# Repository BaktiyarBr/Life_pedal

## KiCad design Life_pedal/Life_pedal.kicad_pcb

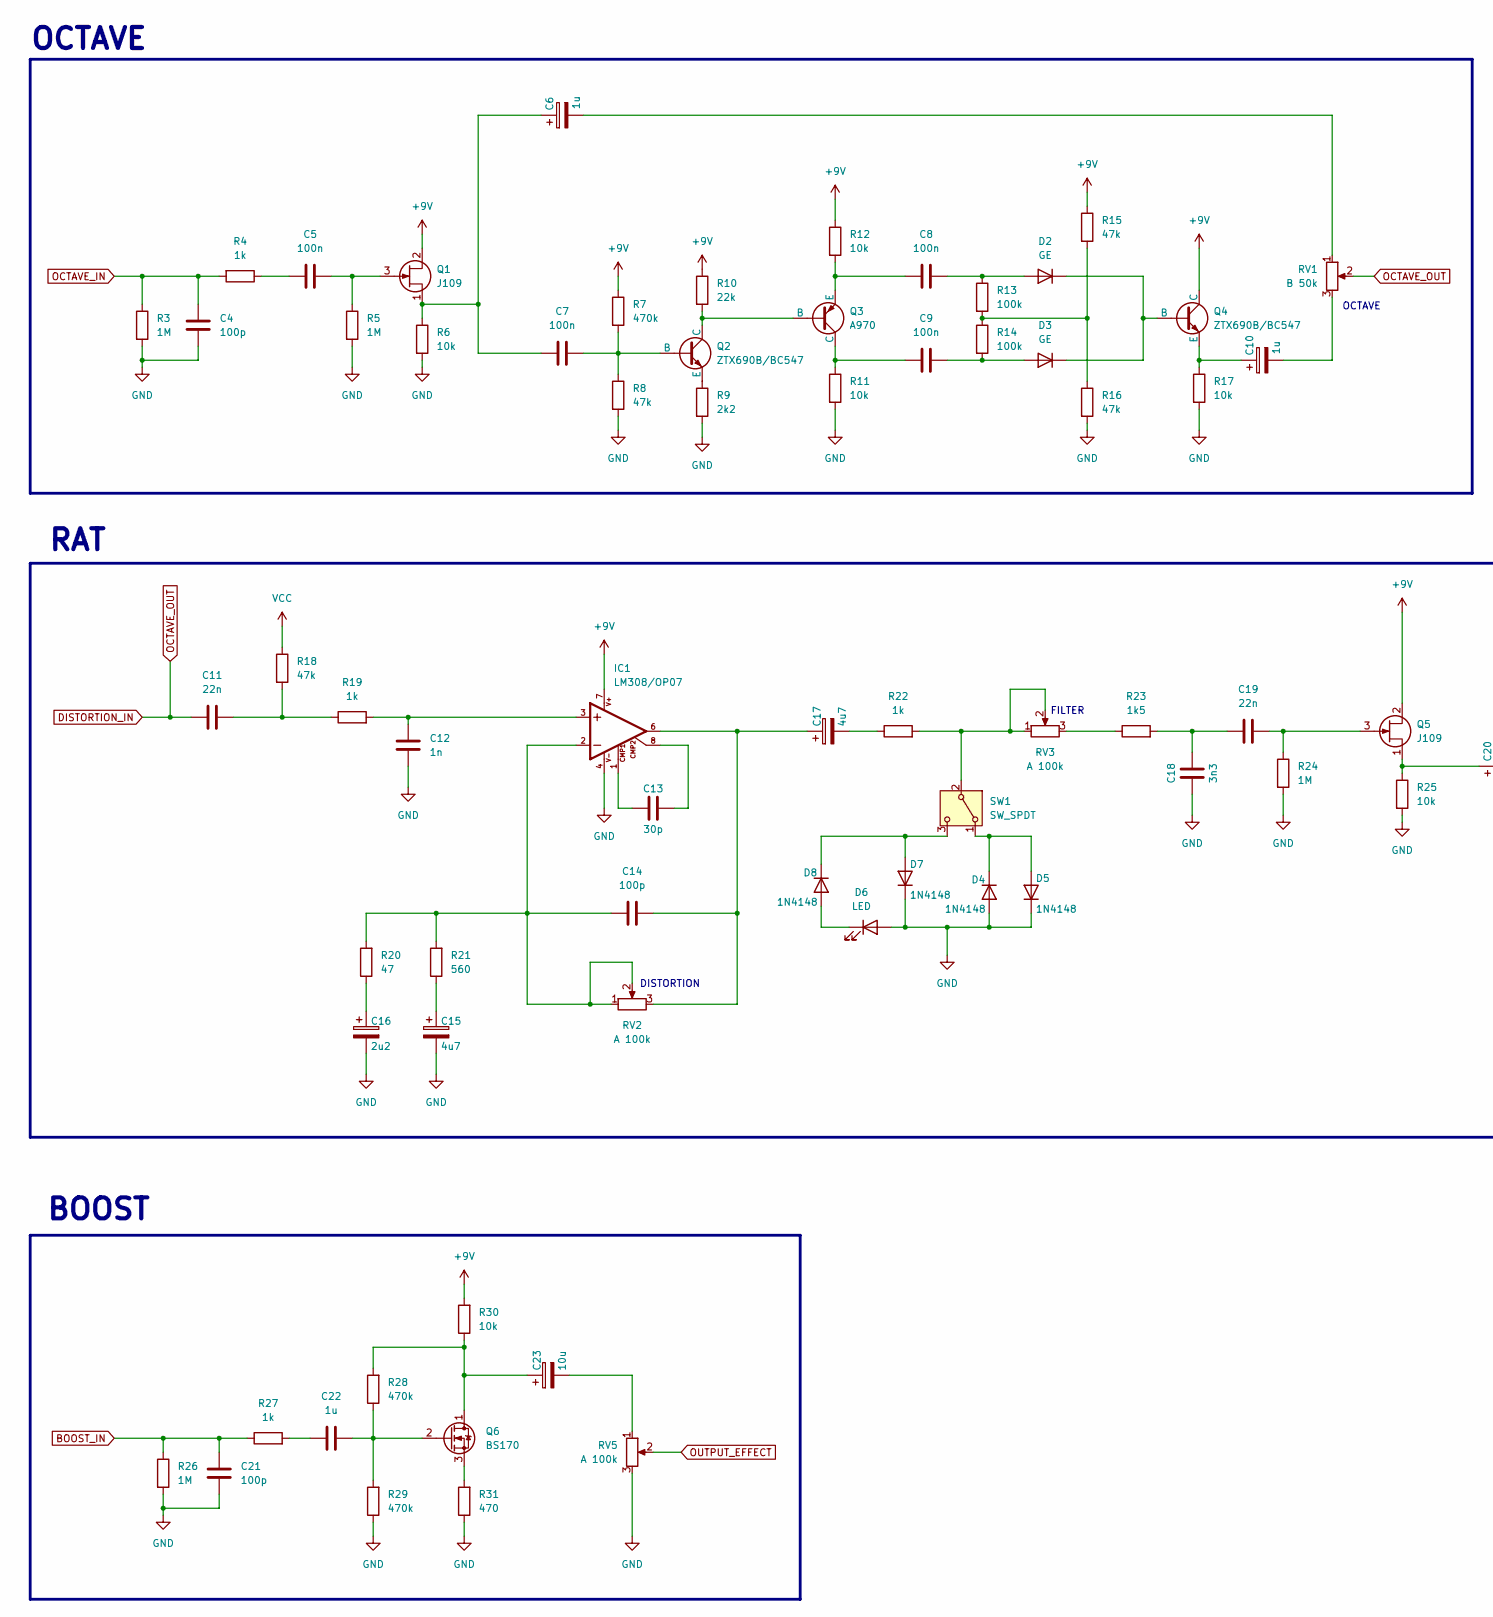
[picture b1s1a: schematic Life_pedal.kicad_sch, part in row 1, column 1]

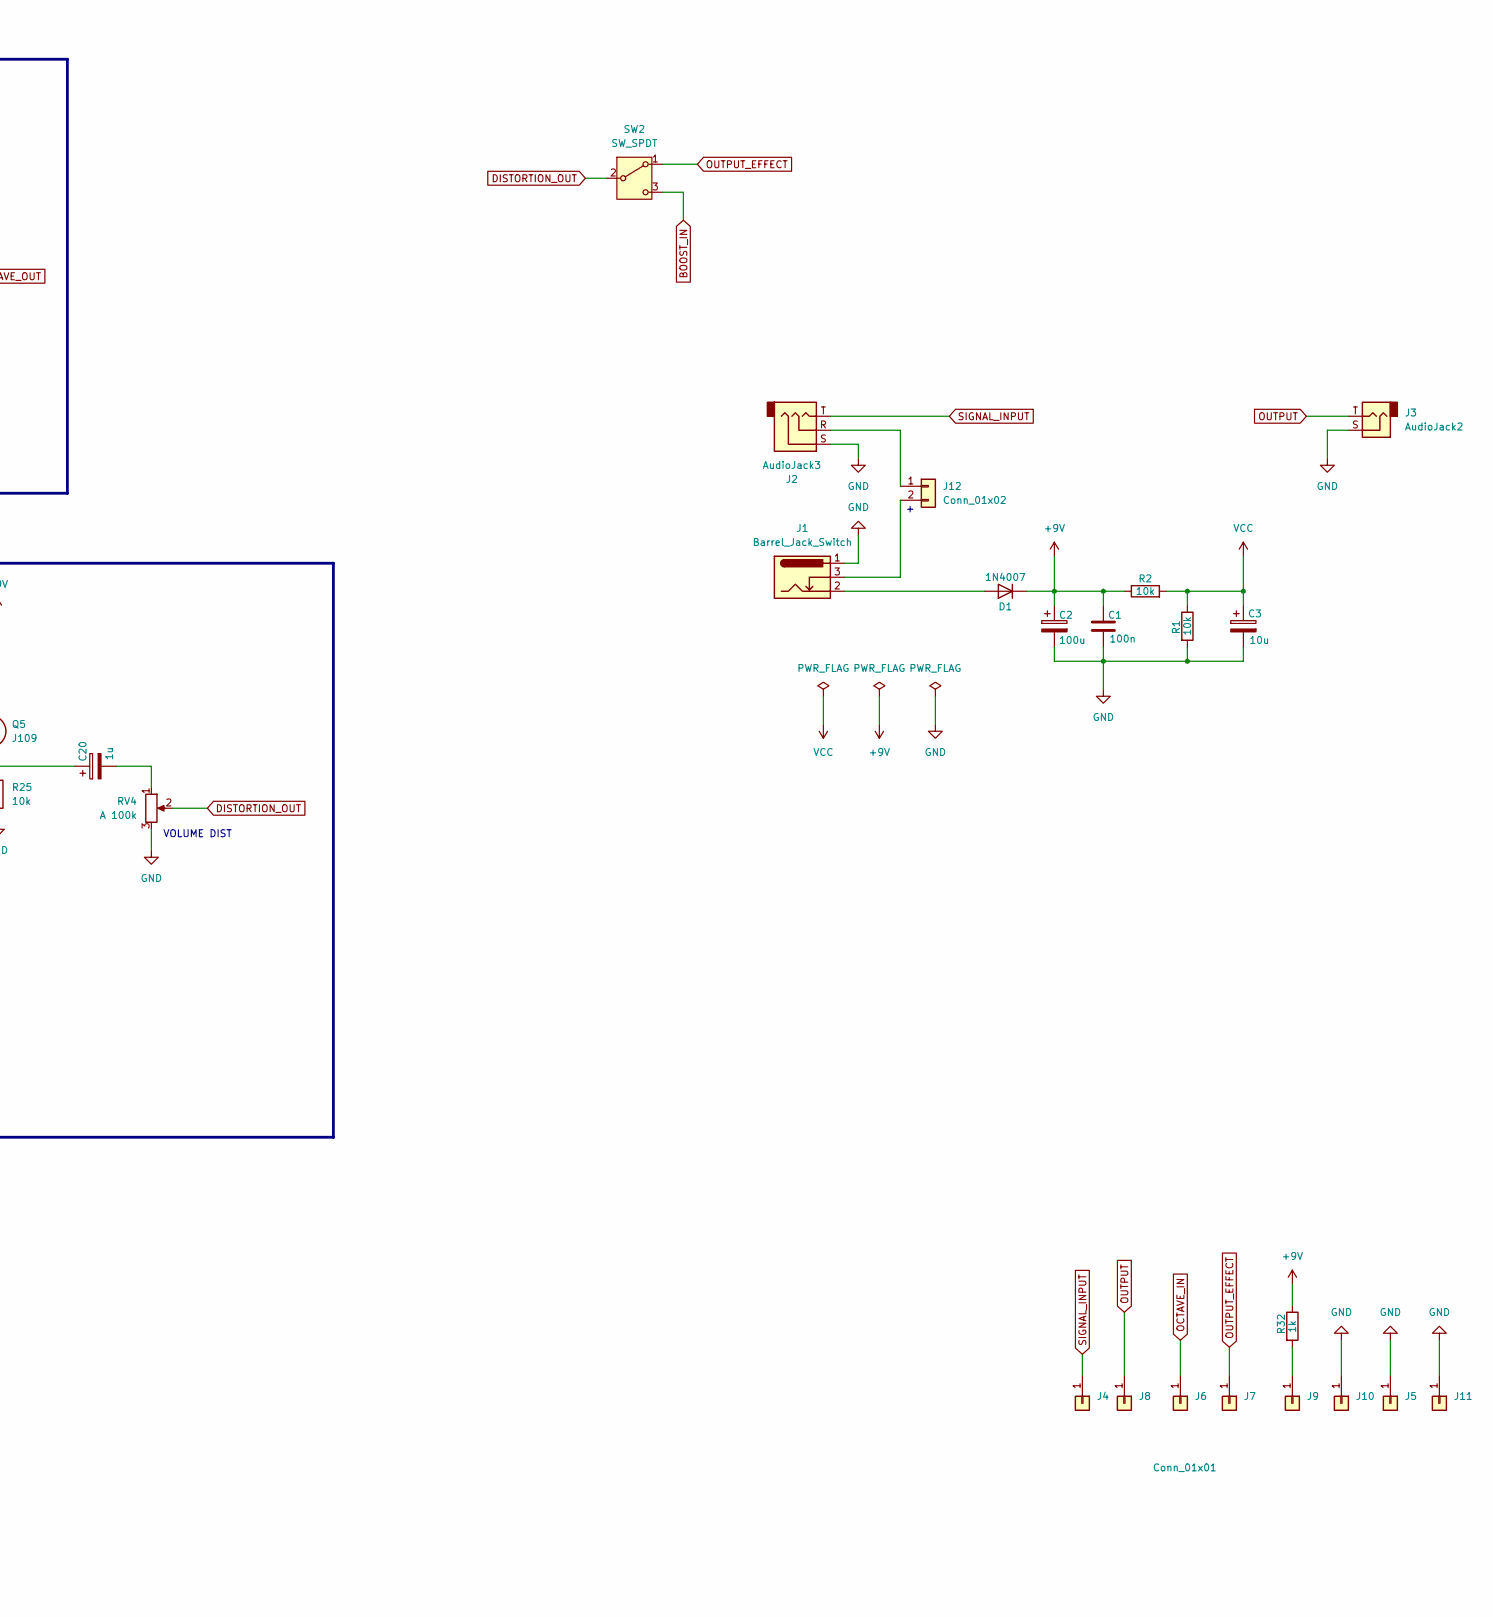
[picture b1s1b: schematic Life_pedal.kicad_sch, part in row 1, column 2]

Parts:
C1, C5, C7, C8, C9: 100n; C_0603_1608Metric_Pad1.08x0.95mm_HandSolder
C2: 100u; CP_Radial_D5.0mm_P2.50mm
C3, C23: 10u; CP_Radial_D5.0mm_P2.50mm
C4, C14, C21: 100p; C_0603_1608Metric_Pad1.08x0.95mm_HandSolder
C6, C10, C20: 1u; CP_Radial_D5.0mm_P2.50mm
C11, C19: 22n; C_0603_1608Metric_Pad1.08x0.95mm_HandSolder
C12: 1n; C_0603_1608Metric_Pad1.08x0.95mm_HandSolder
C13: 30p; C_0603_1608Metric_Pad1.08x0.95mm_HandSolder
C15, C17: 4u7; CP_Radial_D5.0mm_P2.50mm
C16: 2u2; CP_Radial_D5.0mm_P2.50mm
C18: 3n3; C_0603_1608Metric_Pad1.08x0.95mm_HandSolder
C22: 1u; C_0603_1608Metric_Pad1.08x0.95mm_HandSolder
D1: 1N4007; D_DO-41_SOD81_P2.54mm_Vertical_KathodeUp
D2, D3: GE; D_DO-41_SOD81_P2.54mm_Vertical_KathodeUp
D4, D5, D7, D8: 1N4148; D_DO-41_SOD81_P2.54mm_Vertical_KathodeUp
D6: LED; D_DO-41_SOD81_P2.54mm_Vertical_KathodeUp
IC1: LM308/OP07; DIL08
J1: Barrel_Jack_Switch; BarrelJack_GCT_DCJ200-10-A_Horizontal
J2: AudioJack3; Jack_6.35mm_Neutrik_NMJ6HCD2_Horizontal
J3: AudioJack2; Jack_6.35mm_Neutrik_NMJ6HCD2_Horizontal
J4, J5, J6, J7, J8, J9, J10, J11: Conn_01x01; SolderWire-2sqmm_1x01_D2mm_OD3.9mm
J12: Conn_01x02; PinSocket_1x02_P2.54mm_Vertical
Q1, Q5: J109; TO-92L_Inline_Wide
Q2, Q4: ZTX690B/BC547; TO-92L_Inline_Wide
Q3: A970; TO-92L_Inline_Wide
Q6: BS170; TO-92_Inline
R1, R2, R6, R11, R12, R17, R25, R30: 10k; R_0603_1608Metric_Pad0.98x0.95mm_HandSolder
R3, R5, R24, R26: 1M; R_0603_1608Metric_Pad0.98x0.95mm_HandSolder
R4, R19, R22, R27, R32: 1k; R_0603_1608Metric_Pad0.98x0.95mm_HandSolder
R7, R28, R29: 470k; R_0603_1608Metric_Pad0.98x0.95mm_HandSolder
R8, R15, R16, R18: 47k; R_0603_1608Metric_Pad0.98x0.95mm_HandSolder
R9: 2k2; R_0603_1608Metric_Pad0.98x0.95mm_HandSolder
R10: 22k; R_0603_1608Metric_Pad0.98x0.95mm_HandSolder
R13, R14: 100k; R_0603_1608Metric_Pad0.98x0.95mm_HandSolder
R20: 47; R_0603_1608Metric_Pad0.98x0.95mm_HandSolder
R21: 560; R_0603_1608Metric_Pad0.98x0.95mm_HandSolder
R23: 1k5; R_0603_1608Metric_Pad0.98x0.95mm_HandSolder
R31: 470; R_0603_1608Metric_Pad0.98x0.95mm_HandSolder
RV1: B 50k; Potentiometer_Omeg_PC16BU_Vertical
RV2, RV3, RV4, RV5: A 100k; Potentiometer_Omeg_PC16BU_Vertical
SW1, SW2: SW_SPDT; SW_Slide-03_Wuerth-WS-SLTV_10x2.5x6.4_P2.54mm

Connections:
+9V: C1.1, C2.1, D1.1 (K), IC1.7, Q1.2 (S), Q4.1 (C), Q5.2 (S), R2.1, R7.1, R10.1, R12.1, R15.1, R30.2, R32.1
BOOST_IN: C21.1, R26.1, R27.1, SW2.3 (C)
DISTORTION_IN: C11.2, RV1.2
DISTORTION_OUT: RV4.2, SW2.2 (B)
GND: C1.2, C2.2, C3.2, C4.1, C12.2, C15.2, C16.2, C18.1, C21.2, D4.2 (A), D5.1 (K), D6.2 (A), D7.1 (K), IC1.4, J1.1, J2.S, J3.S, J5.1, J10.1, J11.1, R1.2, R3.2, R5.2, R6.2, R8.2, R9.2, R11.2, R16.2, R17.2, R24.2, R25.2, R26.2, R29.1, R31.1, RV4.3, RV5.3
unnamed: C5.2, R4.1
unnamed: C6.2, RV1.1
unnamed: C10.2, RV1.3
unnamed: C11.1, R18.2, R19.1
unnamed: C12.1, IC1.3, R19.2
unnamed: C13.1, IC1.1
unnamed: C13.2, IC1.8
unnamed: C14.1, C17.1, IC1.6, RV2.3
unnamed: C14.2, IC1.2, R20.2, R21.2, RV2.1, RV2.2
unnamed: C15.1, R21.1
unnamed: C16.1, R20.1
unnamed: C17.2, R22.1
unnamed: C18.2, C19.2, R23.2
unnamed: C20.2, RV4.1
unnamed: C22.1, R27.2
unnamed: C23.2, RV5.1
unnamed: D1.2 (A), J1.2
unnamed: C8.1, D2.2 (A), R13.1
unnamed: D2.1 (K), D3.1 (K), Q4.2 (B)
unnamed: C9.1, D3.2 (A), R14.2
unnamed: D4.1 (K), D5.2 (A), SW1.1 (A)
unnamed: D6.1 (K), D8.2 (A)
unnamed: D7.2 (A), D8.1 (K), SW1.3 (C)
unnamed: J9.1, R32.2
unnamed: J2.R, J12.1
unnamed: J1.3, J12.2
unnamed: C6.1, C7.2, Q1.1 (D), R6.1
unnamed: C5.1, Q1.3 (G), R5.1
unnamed: C7.1, Q2.2 (B), R7.2, R8.1
unnamed: Q2.1 (C), Q3.3 (B), R10.2
unnamed: Q2.3 (E), R9.1
unnamed: C9.2, Q3.2 (C), R11.1
unnamed: C8.2, Q3.1 (E), R12.2
unnamed: C10.1, Q4.3 (E), R17.1
unnamed: C20.1, Q5.1 (D), R25.1
unnamed: C19.1, Q5.3 (G), R24.1
unnamed: C23.1, Q6.1 (D), R28.2, R30.1
unnamed: C22.2, Q6.2 (G), R28.1, R29.2
unnamed: Q6.3 (S), R31.2
unnamed: R13.2, R14.1, R15.2, R16.1
unnamed: R23.1, RV3.3
unnamed: R22.2, RV3.1, RV3.2, SW1.2 (B)
OCTAVE_IN: C4.2, J6.1, R3.1, R4.2
OUTPUT: J3.T, J8.1
OUTPUT_EFFECT: J7.1, RV5.2, SW2.1 (A)
SIGNAL_INPUT: J2.T, J4.1
VCC: C3.1, R1.1, R2.2, R18.1

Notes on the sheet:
OCTAVE
BOOST
RAT
VOLUME DIST
DISTORTION
FILTER

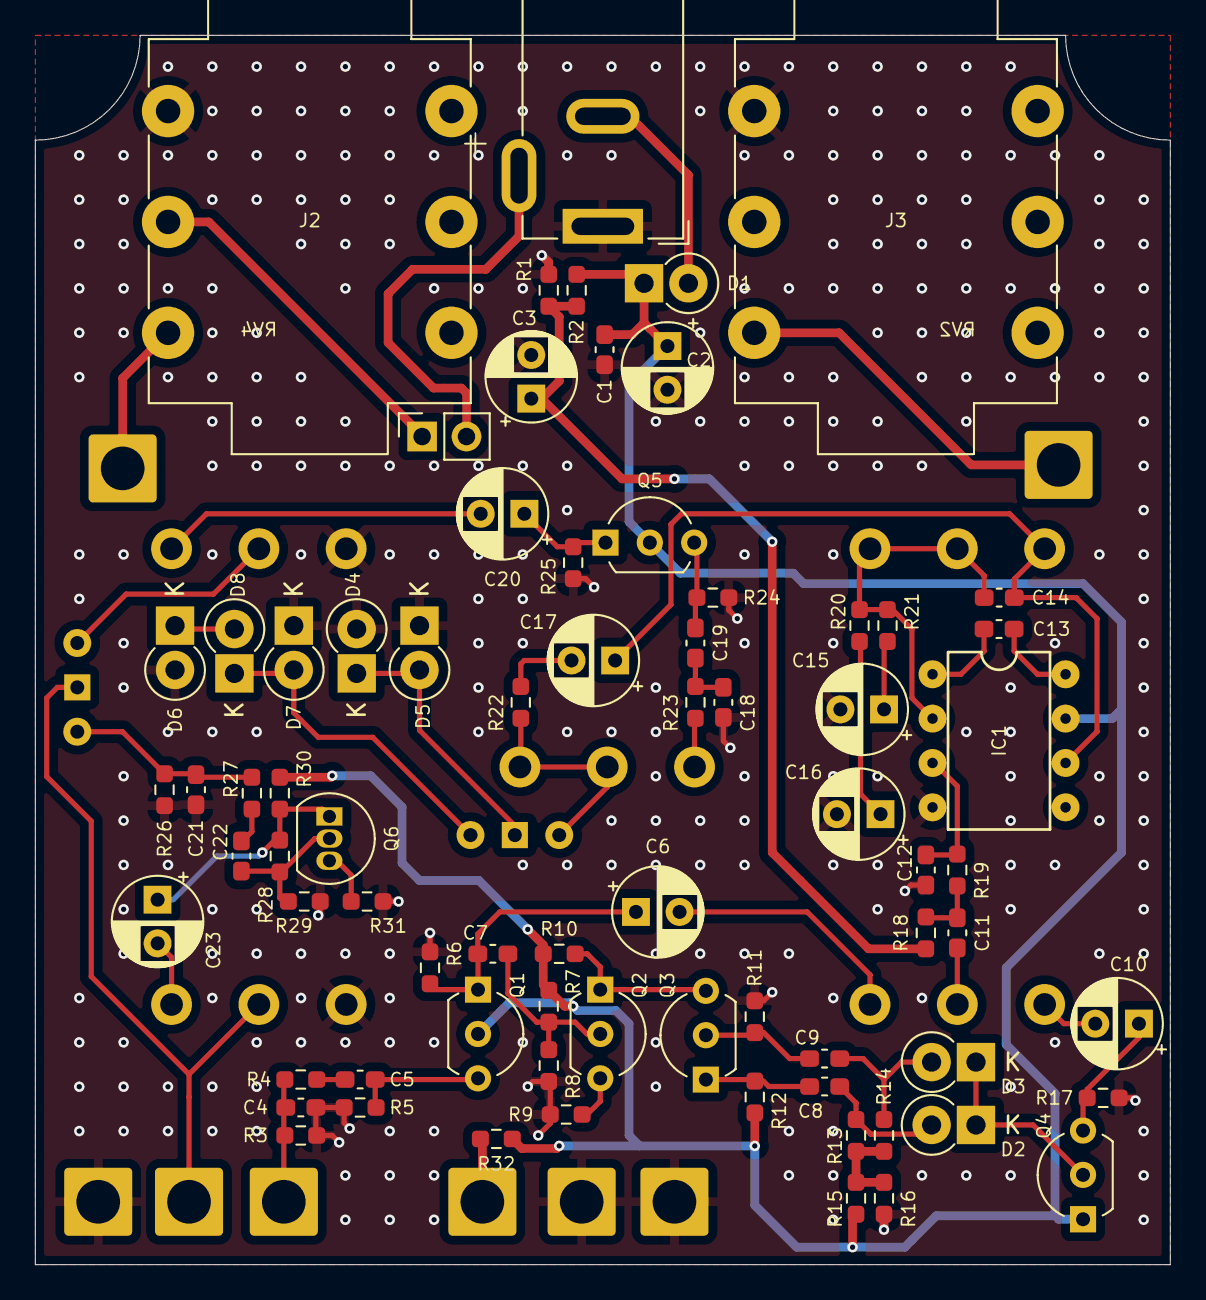
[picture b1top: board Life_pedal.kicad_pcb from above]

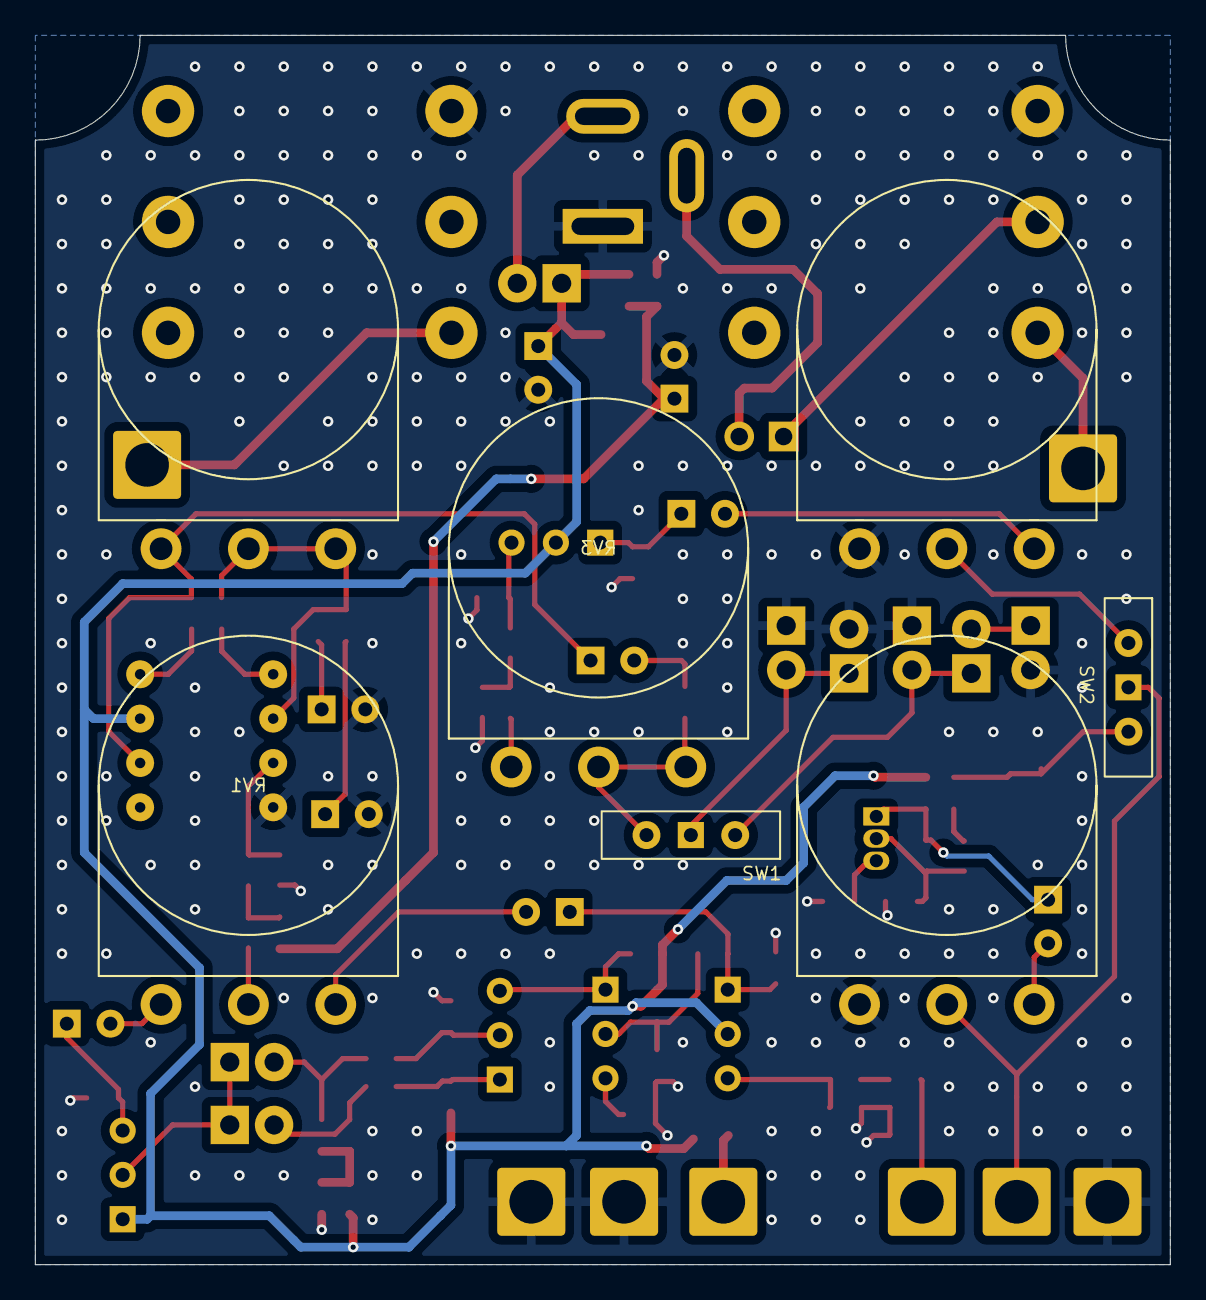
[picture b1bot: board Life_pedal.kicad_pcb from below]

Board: 4 copper layers, 65.0 x 70.4 mm, 89 parts (7 on the bottom side), 52 nets.

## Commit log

2024-07-26 first
2024-09-05 Final
